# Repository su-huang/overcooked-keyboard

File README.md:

# custom end-to-end mechanical keyboard + joystick 
this repository documents the end-to-end hardware engineering of a specialized mechanical keyboard for overcooked2. unlike traditional boards, this project focuses on low-latency analog integration and includes a dedicated joystick to allow for 360-degree movement while maintaining the tactile precision of mechanical switches.

##
i'm currently in the schematic capture and pcb design phase, exploring custom electrical architecture.

key areas of development: 
* joystick integration: developing the circuitry to interface an analog thumbstick (via adc pins) alongside a traditional switch matrix
* circuit analysis: conducting research into matrix scanning logic and signal integrity to ensure zero-latency response times during peak gameplay
* pcb layout: routing the traces for a custom form factor, prioritizing ergonomic joystick placement to reduce thumb strain

roadmap: 
  * custom firmware: writing specialized qmk/zmk logic to map the joystick as an x-input controller or high-speed directional keys
  * fabrication: sending the first revision of the pcb for manufacturing and hand-soldering the smd components
  * enclosure design: cad modelling a low-profile case that supports the extra vertical height of the joystick assembly
  * custom configuration gui: allowing real-time customization without requiring the user to recompile c code or flash firmware manually

technical stack: 
  * eda: kicad 
  * cad: onshape 
  * microcontroller: rp2040
  * input hardware: mechanical switches + 2-axis analog potentiometer
  * firmware: qmk with custom analog-to-hid mapping logic
  * target performance: 1000hz polling rate for frame-perfect dashing

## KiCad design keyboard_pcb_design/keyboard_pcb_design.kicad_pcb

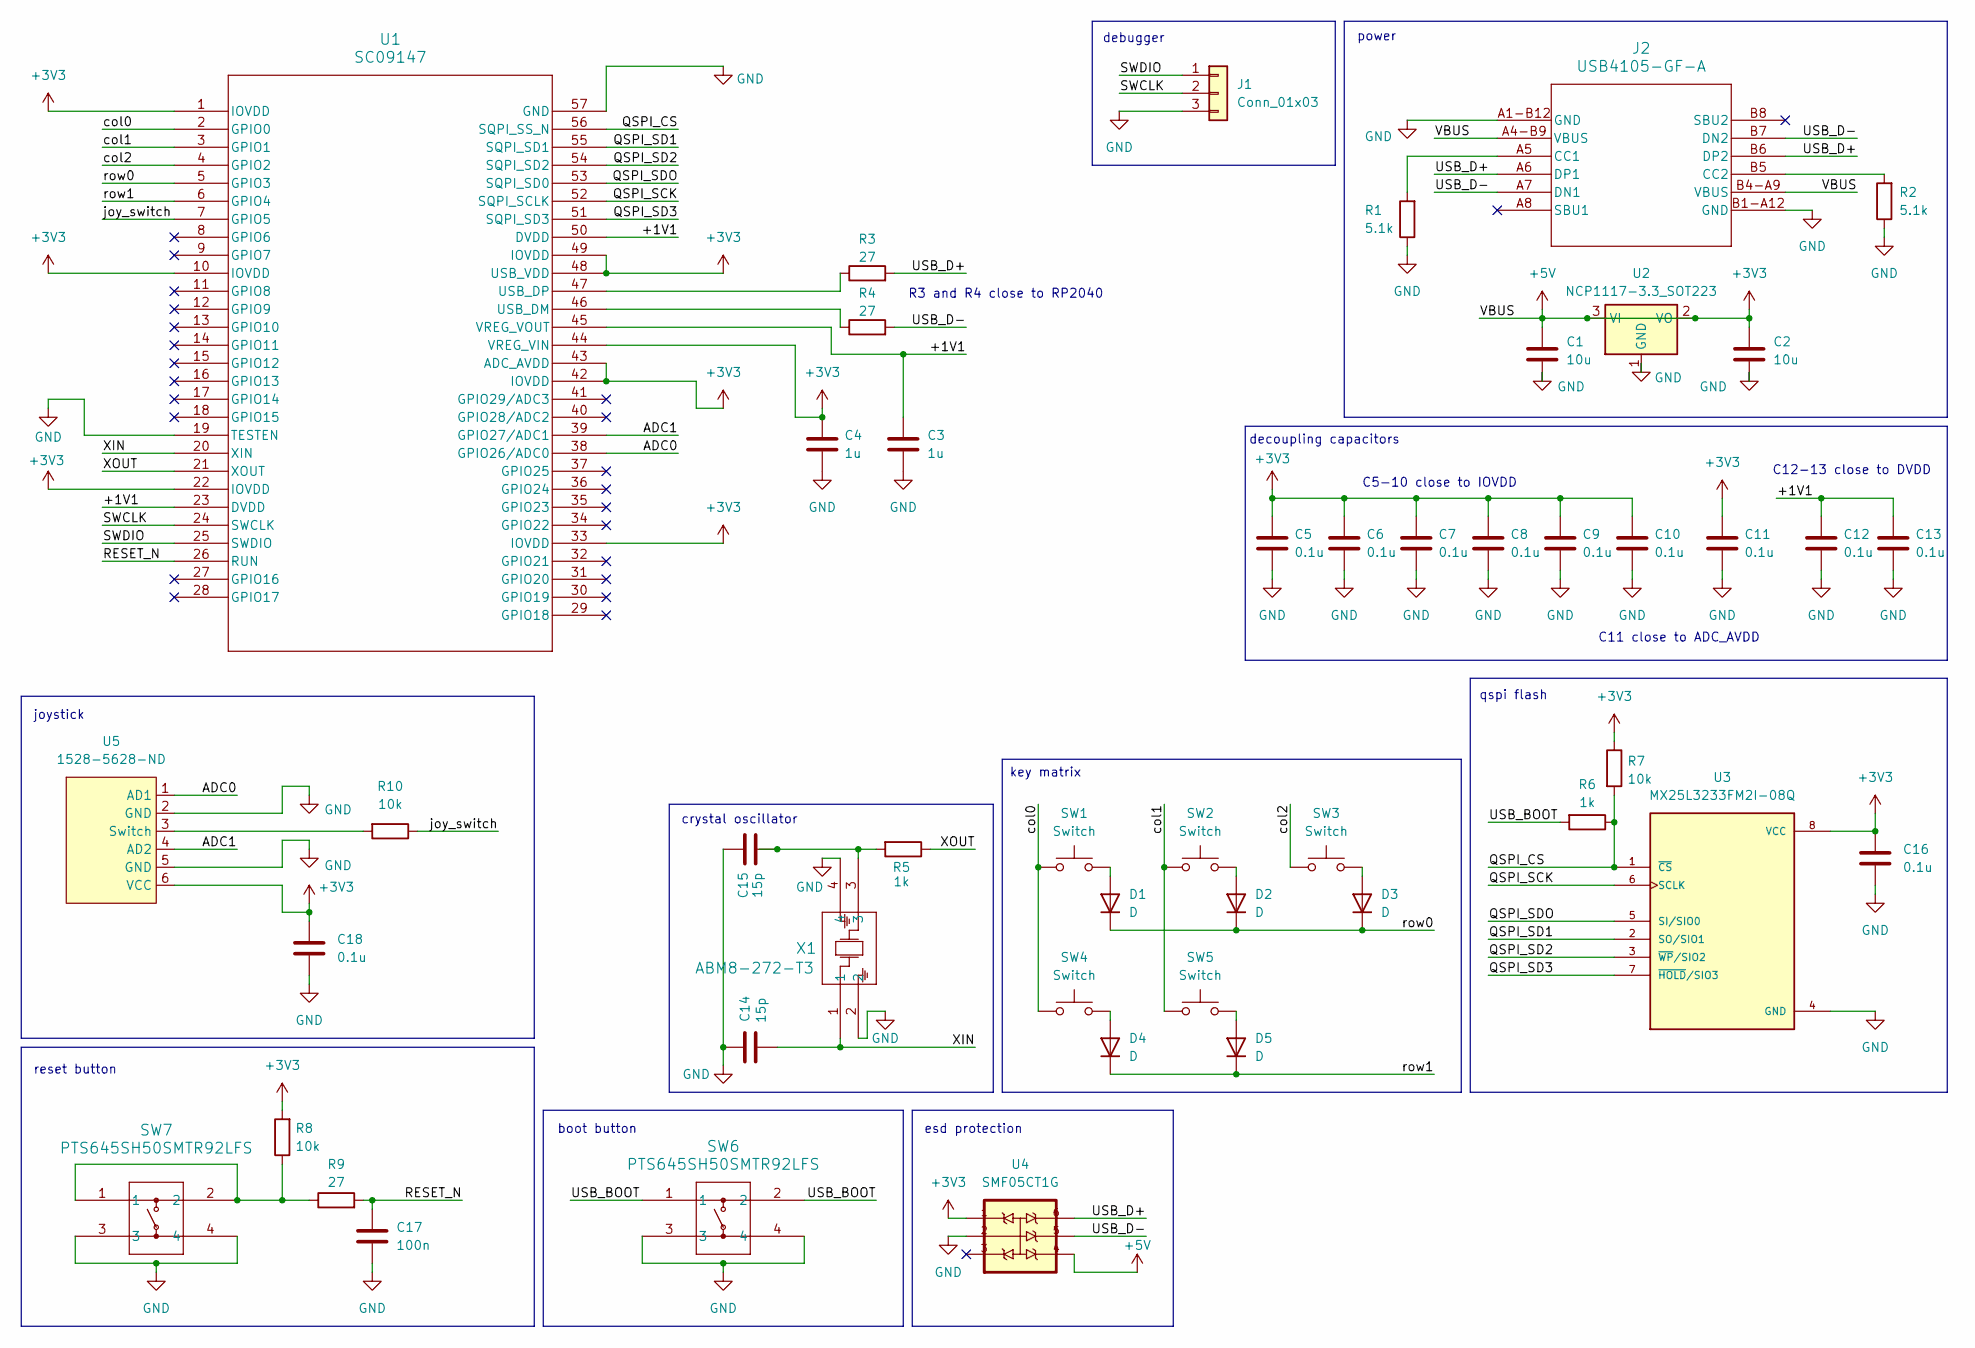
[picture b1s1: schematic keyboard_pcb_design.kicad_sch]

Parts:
C1, C2: 10u; C_0201_0603Metric
C3, C4: 1u; C_0201_0603Metric
C5, C6, C7, C8, C9, C10, C11, C12, C13, C16, C18: 0.1u; C_0201_0603Metric
C14, C15: 15p; C_0201_0603Metric
C17: 100n; C_0201_0603Metric
D1, D2, D3, D4, D5: D; D_0201_0603Metric
J1: Conn_01x03; PinHeader_1x03_P2.54mm_Horizontal
J2: USB4105-GF-A; USB4105_GCT
R1, R2: 5.1k; R_0201_0603Metric
R3, R4, R9: 27; R_0201_0603Metric
R5, R6: 1k; R_0201_0603Metric
R7, R8, R10: 10k; R_0201_0603Metric
SW1, SW2, SW3, SW4, SW5: Switch; SW_SPST_TL3342
SW6, SW7: PTS645SH50SMTR92LFS; PTS645SL50SMTR92 LFS
U1: SC09147; SC09147_QFN56_7X7_RPI
U2: NCP1117-3.3_SOT223; SOT-223-3_TabPin2
U3: MX25L3233FM2I-08Q
U4: SMF05CT1G; SOT65P210X110-6N
U5: 1528-5628-ND
X1: ABM8-272-T3; XTAL_ABM8-272-T3

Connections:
/+1V1: C3.1, C12.1, C13.1, U1.23 (DVDD), U1.45 (VREG_VOUT), U1.50 (DVDD)
/ADC0: U1.38 (GPIO26/ADC0), U5.1 (AD1)
/ADC1: U1.39 (GPIO27/ADC1), U5.4 (AD2)
/QSPI_CS: R6.1, R7.2, U1.56 (SQPI_SS_N), U3.1 (~CS)
/QSPI_SCK: U1.52 (SQPI_SCLK), U3.6 (SCLK)
/QSPI_SD1: U1.55 (SQPI_SD1), U3.2 (SO/SIO1)
/QSPI_SD2: U1.54 (SQPI_SD2), U3.3 (~WP/SIO2)
/QSPI_SD3: U1.51 (SQPI_SD3), U3.7 (~HOLD/SIO3)
/QSPI_SDO: U1.53 (SQPI_SD0), U3.5 (SI/SIO0)
/RESET_N: C17.1, R9.2, U1.26 (RUN)
/SWCLK: J1.2, U1.24 (SWCLK)
/SWDIO: J1.1, U1.25 (SWDIO)
/USB_BOOT: R6.2, SW6.1, SW6.2
/USB_D+: J2.A6 (DP1), J2.B6 (DP2), R3.2, U4.6
/USB_D-: J2.A7 (DN1), J2.B7 (DN2), R4.2, U4.5
/XIN: C14.1, U1.20 (XIN), X1.1
/XOUT: R5.1, U1.21 (XOUT)
/col0: SW1.1, SW4.1, U1.2 (GPIO0)
/col1: SW2.1, SW5.1, U1.3 (GPIO1)
/col2: SW3.1, U1.4 (GPIO2)
/joy_switch: R10.1, U1.7 (GPIO5)
/row0: D1.1 (K), D2.1 (K), D3.1 (K), U1.5 (GPIO3)
/row1: D4.1 (K), D5.1 (K), U1.6 (GPIO4)
GND: C1.2, C2.2, C3.2, C4.2, C5.2, C6.2, C7.2, C8.2, C9.2, C10.2, C11.2, C12.2, C13.2, C14.2, C15.1, C16.2, C17.2, C18.2, J1.3, J2.A1-B12 (GND), J2.B1-A12 (GND), R1.1, R2.1, SW6.3, SW6.4, SW7.3, SW7.4, U1.19 (TESTEN), U1.57 (GND), U2.1 (GND), U3.4 (GND), U4.2, U5.2 (GND), U5.5 (GND), X1.2, X1.4
unnamed: C15.2, R5.2, X1.3
unnamed: D1.2 (A), SW1.2
unnamed: D2.2 (A), SW2.2
unnamed: D3.2 (A), SW3.2
unnamed: D4.2 (A), SW4.2
unnamed: D5.2 (A), SW5.2
unnamed: J2.A5 (CC1), R1.2
unnamed: J2.B5 (CC2), R2.2
unnamed: R8.1, R9.1, SW7.1, SW7.2
unnamed: R4.1, U1.46 (USB_DM)
unnamed: R3.1, U1.47 (USB_DP)
unnamed: R10.2, U5.3 (Switch)

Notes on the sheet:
joystick
R3 and R4 close to RP2040
crystal oscillator
esd protection
power
boot button
reset button
key matrix
debugger
qspi flash
C5-10 close to IOVDD
decoupling capacitors
C12-13 close to DVDD
C11 close to ADC_AVDD

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
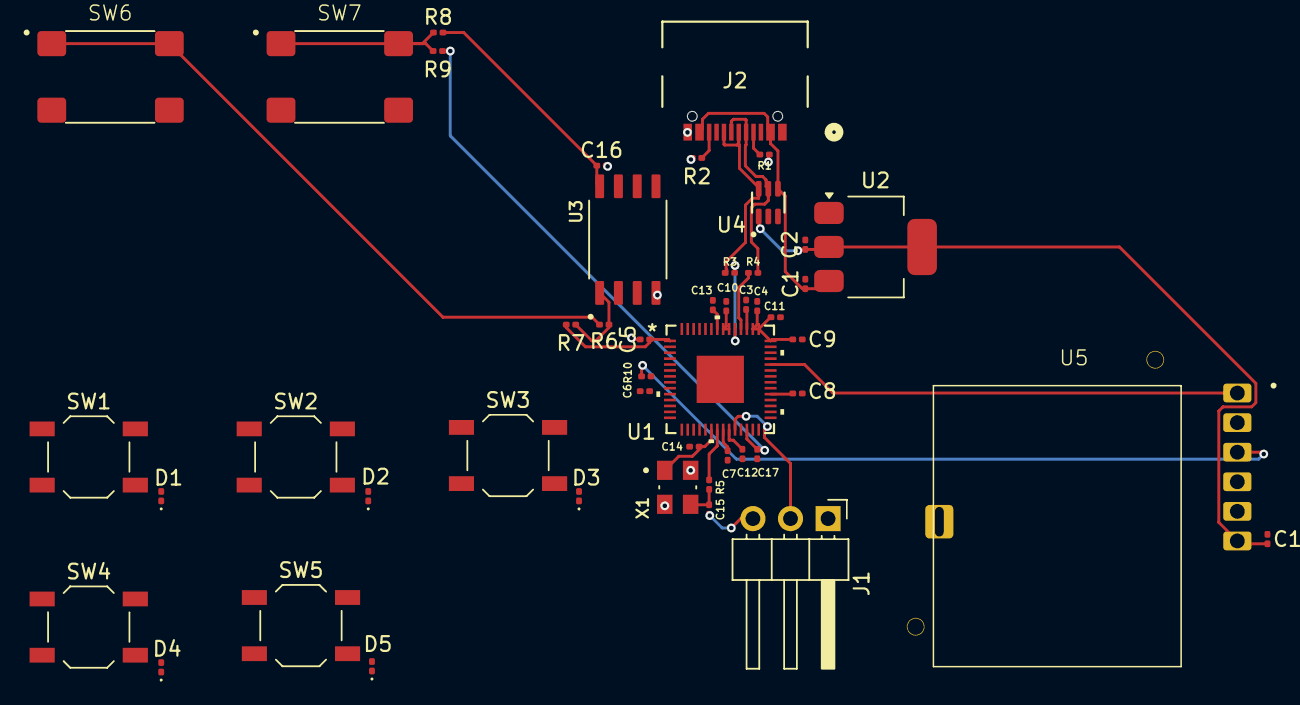
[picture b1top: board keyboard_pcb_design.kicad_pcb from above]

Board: 2 copper layers, 48 parts (0 on the bottom side), 38 nets.

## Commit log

2026-02-05 imported rp2040 symbol and footprint
2026-02-05 completed input supply schematic
2026-02-07 completed decoupling capacitors schematics
2026-02-08 uploaded crystal symbol and footprint
2026-02-08 complete crystal oscillator
2026-02-08 saved crystal oscillator schematic
2026-02-10 flash storage schematic wip
2026-02-10 uploaded flash storage symbol and footprint
2026-02-11 updated flash storage component
2026-02-11 completed qspi flash storage schematic
2026-02-15 add switch library
2026-02-16 key matrix schematic
2026-02-16 change switch library
2026-02-16 save backups
2026-02-16 tvs diode for esd protection
2026-02-16 complete esd protection schematic
2026-02-18 update usbc and add footprints
2026-02-18 saved changes
2026-02-19 update usb symbol and add switch button
2026-02-19 update schematic for to usbc 16p and reset/boot buttons
2026-03-03 debug conn schematic
2026-03-03 fix iovdd connection
2026-03-03 add readme
2026-03-03 fix typo
2026-03-07 create joystick footprint
2026-03-07 create joystick symbol
2026-03-07 complete joystick schematic
2026-03-09 update custom footprints
2026-03-09 assign footprints to symbols
2026-03-19 begin pcd layout
2026-03-22 fix formatting
2026-04-07 update readme formatting
2026-06-08 remove ds store
2026-06-08 revision
2026-06-09 reorg
